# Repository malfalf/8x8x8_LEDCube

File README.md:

# 8x8x8_LEDCube
PCB con componentes necesarios para controlar un cubo de 8x8x8 LEDs RGB

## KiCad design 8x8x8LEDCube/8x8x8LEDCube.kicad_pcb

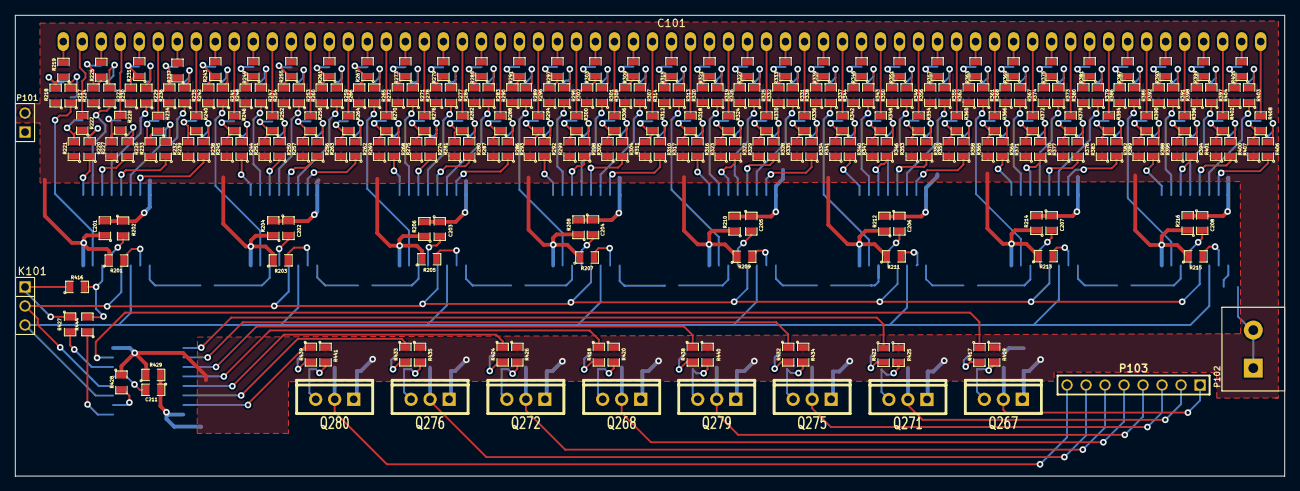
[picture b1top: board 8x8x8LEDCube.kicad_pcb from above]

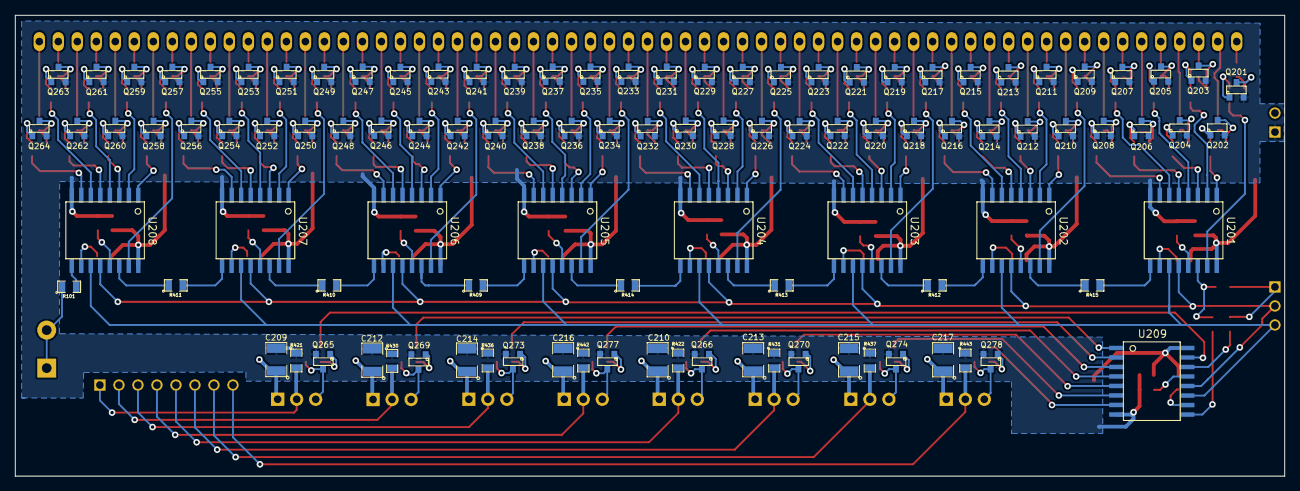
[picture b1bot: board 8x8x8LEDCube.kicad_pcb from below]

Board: 2 copper layers, 169.6 x 61.6 mm, 356 parts (105 on the bottom side), 330 nets.

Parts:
C101: CONNECTOR_1X64; 1x64_Connector_Receptade_2.54mm
C201, C202, C203, C204, C205, C206, C207, C208, C211: 0.1u; SM0805_NoVal
C209, C210, C212, C213, C214, C215, C216, C217: 47U; SM1210
K101: CONN_3; PIN_ARRAY_3X1
P101: CONN_2; PIN_ARRAY_2X1
P102: CONN_2; Terminal_Block_200mil_5mm
P103: CONN_8; PIN_ARRAY_8x1
Q201, Q202, Q203, Q204, Q205, Q206, Q207, Q208, Q209, Q210, Q211, Q212, Q213, Q214, Q215, Q216, Q217, Q218, Q219, Q220, Q221, Q222, Q223, Q224, Q225, Q226, Q227, Q228, Q229, Q230, Q231, Q232, Q233, Q234, Q235, Q236, Q237, Q238, Q239, Q240, Q241, Q242, Q243, Q244, Q245, Q246, Q247, Q248, Q249, Q250, Q251, Q252, Q253, Q254, Q255, Q256, Q257, Q258, Q259, Q260, Q261, Q262, Q263, Q264, Q265, Q266, Q269, Q270, Q273, Q274, Q277, Q278: NPN; SOT23_NPN_MMBT3904
Q267, Q268, Q271, Q272, Q275, Q276, Q279, Q280: IRF9540N; TO220_IRF9540N
R101, R201, R202, R203, R204, R205, R206, R207, R208, R209, R210, R211, R212, R213, R214, R215, R216, R409, R410, R411, R412, R413, R414, R415, R416, R427, R428, R429, R444: 0; SM0805_NoVal
R217, R218, R220, R221, R223, R224, R226, R227, R229, R230, R232, R233, R235, R236, R238, R239, R241, R242, R244, R245, R247, R248, R250, R251, R253, R254, R256, R257, R259, R260, R262, R263, R265, R266, R268, R269, R271, R272, R274, R275, R277, R278, R280, R281, R283, R284, R286, R287, R289, R290, R292, R293, R295, R296, R298, R299, R301, R302, R304, R305, R307, R308, R310, R311, R313, R314, R316, R317, R319, R320, R322, R323, R325, R326, R328, R329, R331, R332, R334, R335, R337, R338, R340, R341, R343, R344, R346, R347, R349, R350, R352, R353, R355, R356, R358, R359, R361, R362, R364, R365, R367, R368, R370, R371, R373, R374, R376, R377, R379, R380, R382, R383, R385, R386, R388, R389, R391, R392, R394, R395, R397, R398, R400, R401, R403, R404, R406, R407, R417, R418, R419, R420, R423, R424, R425, R426, R432, R433, R434, R435, R438, R439, R440, R441: 1K; SM0805_NoVal
R219, R222, R225, R228, R231, R234, R237, R240, R243, R246, R249, R252, R255, R258, R261, R264, R267, R270, R273, R276, R279, R282, R285, R288, R291, R294, R297, R300, R303, R306, R309, R312, R315, R318, R321, R324, R327, R330, R333, R336, R339, R342, R345, R348, R351, R354, R357, R360, R363, R366, R369, R372, R375, R378, R381, R384, R387, R390, R393, R396, R399, R402, R405, R408, R421, R422, R430, R431, R436, R437, R442, R443: 100; SM0805_NoVal
U201, U202, U203, U204, U205, U206, U207, U208, U209: SN74HC595DWR; SOIC16_SN74HC595DWR

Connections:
/AnodeControl/AnodeP1: P103.1, Q267.D, R421.2
/AnodeControl/AnodeP2: P103.2, Q271.D, R430.2
/AnodeControl/AnodeP3: P103.3, Q275.D, R436.2
/AnodeControl/AnodeP4: P103.4, Q279.D, R442.2
/AnodeControl/AnodeP5: P103.5, Q268.D, R422.2
/AnodeControl/AnodeP6: P103.6, Q272.D, R431.2
/AnodeControl/AnodeP7: P103.7, Q276.D, R437.2
/AnodeControl/AnodeP8: P103.8, Q280.D, R443.2
/ColorControl/C1Red: C101.1, R219.2
/ColorControl/C2Red: C101.2, R222.2
/ColorControl/C3Red: C101.3, R225.2
/ColorControl/C4Red: C101.4, R228.2
/ColorControl/C5Red: C101.5, R231.2
/ColorControl/C6Red: C101.6, R234.2
/ColorControl/C7Red: C101.7, R237.2
/ColorControl/C8Red: C101.8, R240.2
/ColorControl/C9Red: C101.9, R243.2
/ColorControl/C10Red: C101.10, R246.2
/ColorControl/C11Red: C101.11, R249.2
/ColorControl/C12Red: C101.12, R252.2
/ColorControl/C13Red: C101.13, R255.2
/ColorControl/C14Red: C101.14, R258.2
/ColorControl/C15Red: C101.15, R261.2
/ColorControl/C16Red: C101.16, R264.2
/ColorControl/C17Red: C101.17, R267.2
/ColorControl/C18Red: C101.18, R270.2
/ColorControl/C19Red: C101.19, R273.2
/ColorControl/C20Red: C101.20, R276.2
/ColorControl/C21Red: C101.21, R279.2
/ColorControl/C22Red: C101.22, R282.2
/ColorControl/C23Red: C101.23, R285.2
/ColorControl/C24Red: C101.24, R288.2
/ColorControl/C25Red: C101.25, R291.2
/ColorControl/C26Red: C101.26, R294.2
/ColorControl/C27Red: C101.27, R297.2
/ColorControl/C28Red: C101.28, R300.2
/ColorControl/C29Red: C101.29, R303.2
/ColorControl/C30Red: C101.30, R306.2
/ColorControl/C31Red: C101.31, R309.2
/ColorControl/C32Red: C101.32, R312.2
/ColorControl/C33Red: C101.33, R315.2
/ColorControl/C34Red: C101.34, R318.2
/ColorControl/C35Red: C101.35, R321.2
/ColorControl/C36Red: C101.36, R324.2
/ColorControl/C37Red: C101.37, R327.2
/ColorControl/C38Red: C101.38, R330.2
/ColorControl/C39Red: C101.39, R333.2
/ColorControl/C40Red: C101.40, R336.2
/ColorControl/C41Red: C101.41, R339.2
/ColorControl/C42Red: C101.42, R342.2
/ColorControl/C43Red: C101.43, R345.2
/ColorControl/C44Red: C101.44, R348.2
/ColorControl/C45Red: C101.45, R351.2
/ColorControl/C46Red: C101.46, R354.2
/ColorControl/C47Red: C101.47, R357.2
/ColorControl/C48Red: C101.48, R360.2
/ColorControl/C49Red: C101.49, R363.2
/ColorControl/C50Red: C101.50, R366.2
/ColorControl/C51Red: C101.51, R369.2
/ColorControl/C52Red: C101.52, R372.2
/ColorControl/C53Red: C101.53, R375.2
/ColorControl/C54Red: C101.54, R378.2
/ColorControl/C55Red: C101.55, R381.2
/ColorControl/C56Red: C101.56, R384.2
/ColorControl/C57Red: C101.57, R387.2
/ColorControl/C58Red: C101.58, R390.2
/ColorControl/C59Red: C101.59, R393.2
/ColorControl/C60Red: C101.60, R396.2
/ColorControl/C61Red: C101.61, R399.2
/ColorControl/C62Red: C101.62, R402.2
/ColorControl/C63Red: C101.63, R405.2
/ColorControl/C64Red: C101.64, R408.2
/ColorControl/NextColor: R101.2, U208.9
AnodePlane1: R417.1, U209.15
AnodePlane2: R423.1, U209.1
AnodePlane3: R432.1, U209.2
AnodePlane4: R438.1, U209.3
AnodePlane5: R418.1, U209.4
AnodePlane6: R424.1, U209.5
AnodePlane7: R433.1, U209.6
AnodePlane8: R439.1, U209.7
DATA_IN: K101.1, R416.1, R427.1
FIRST_COLOR: R444.1, U209.9
GND: C201.2, C202.2, C203.2, C204.2, C205.2, C206.2, C207.2, C208.2, C209.2, C210.2, C211.2, C212.2, C213.2, C214.2, C215.2, C216.2, C217.2, P101.1, Q201.1, Q202.1, Q203.1, Q204.1, Q205.1, Q206.1, Q207.1, Q208.1, Q209.1, Q210.1, Q211.1, Q212.1, Q213.1, Q214.1, Q215.1, Q216.1, Q217.1, Q218.1, Q219.1, Q220.1, Q221.1, Q222.1, Q223.1, Q224.1, Q225.1, Q226.1, Q227.1, Q228.1, Q229.1, Q230.1, Q231.1, Q232.1, Q233.1, Q234.1, Q235.1, Q236.1, Q237.1, Q238.1, Q239.1, Q240.1, Q241.1, Q242.1, Q243.1, Q244.1, Q245.1, Q246.1, Q247.1, Q248.1, Q249.1, Q250.1, Q251.1, Q252.1, Q253.1, Q254.1, Q255.1, Q256.1, Q257.1, Q258.1, Q259.1, Q260.1, Q261.1, Q262.1, Q263.1, Q264.1, Q265.1, Q266.1, Q269.1, Q270.1, Q273.1, Q274.1, Q277.1, Q278.1, R202.1, R204.1, R206.1, R208.1, R210.1, R212.1, R214.1, R216.1, R421.1, R422.1, R429.1, R430.1, R431.1, R436.1, R437.1, R442.1, R443.1, U201.8, U202.8, U203.8, U204.8, U205.8, U206.8, U207.8, U208.8, U209.8
LATCH: K101.2, U201.12, U202.12, U203.12, U204.12, U205.12, U206.12, U207.12, U208.12, U209.12
unnamed: P102.1, P102.2, R101.1
unnamed: Q237.3, R326.2, R327.1
unnamed: Q237.2, R325.2
unnamed: Q238.2, R328.2
unnamed: Q235.2, R319.2
unnamed: Q235.3, R320.2, R321.1
unnamed: Q236.3, R323.2, R324.1
unnamed: Q236.2, R322.2
unnamed: Q233.3, R314.2, R315.1
unnamed: Q233.2, R313.2
unnamed: Q234.2, R316.2
unnamed: Q234.3, R317.2, R318.1
unnamed: Q239.2, R331.2
unnamed: Q240.3, R335.2, R336.1
unnamed: Q240.2, R334.2
unnamed: Q230.3, R305.2, R306.1
unnamed: Q238.3, R329.2, R330.1
unnamed: Q241.3, R338.2, R339.1
unnamed: Q244.3, R347.2, R348.1
unnamed: Q244.2, R346.2
unnamed: Q245.3, R350.2, R351.1
unnamed: Q241.2, R337.2
unnamed: Q242.3, R341.2, R342.1
unnamed: Q242.2, R340.2
unnamed: Q243.2, R343.2
unnamed: Q243.3, R344.2, R345.1
unnamed: Q239.3, R332.2, R333.1
unnamed: Q255.2, R379.2
unnamed: Q224.3, R287.2, R288.1
unnamed: Q224.2, R286.2
unnamed: Q222.3, R281.2, R282.1
unnamed: Q222.2, R280.2
unnamed: Q217.2, R265.2
unnamed: Q223.3, R284.2, R285.1
unnamed: Q223.2, R283.2
unnamed: Q221.2, R277.2
unnamed: Q221.3, R278.2, R279.1
unnamed: Q220.3, R275.2, R276.1
unnamed: Q217.3, R266.2, R267.1
unnamed: Q218.2, R268.2
unnamed: Q218.3, R269.2, R270.1
unnamed: Q219.2, R271.2
unnamed: Q219.3, R272.2, R273.1
unnamed: Q220.2, R274.2
unnamed: Q228.2, R298.2
unnamed: Q226.3, R293.2, R294.1
unnamed: Q227.2, R295.2
unnamed: Q227.3, R296.2, R297.1
unnamed: Q226.2, R292.2
unnamed: Q228.3, R299.2, R300.1
unnamed: Q229.2, R301.2
unnamed: Q229.3, R302.2, R303.1
unnamed: Q232.2, R310.2
unnamed: Q225.2, R289.2
unnamed: Q225.3, R290.2, R291.1
unnamed: Q230.2, R304.2
unnamed: Q231.2, R307.2
unnamed: Q231.3, R308.2, R309.1
unnamed: Q232.3, R311.2, R312.1
unnamed: Q261.3, R398.2, R399.1
unnamed: Q261.2, R397.2
unnamed: Q262.3, R401.2, R402.1
unnamed: Q262.2, R400.2
unnamed: Q258.2, R388.2
unnamed: Q259.2, R391.2
unnamed: Q259.3, R392.2, R393.1
unnamed: Q260.2, R394.2
unnamed: Q260.3, R395.2, R396.1
unnamed: Q257.2, R385.2
unnamed: Q257.3, R386.2, R387.1
unnamed: Q258.3, R389.2, R390.1
unnamed: Q263.3, R404.2, R405.1
unnamed: Q263.2, R403.2
unnamed: Q264.3, R407.2, R408.1
unnamed: Q264.2, R406.2
unnamed: Q254.3, R377.2, R378.1
unnamed: R413.2, U203.9
unnamed: R414.2, U204.9
unnamed: R409.2, U205.9
unnamed: R410.2, U206.9
unnamed: R411.2, U207.9
unnamed: R416.2, R444.2, U201.14
unnamed: R415.2, U201.9
unnamed: Q248.2, R358.2
unnamed: Q248.3, R359.2, R360.1
unnamed: Q245.2, R349.2
unnamed: Q246.2, R352.2
unnamed: Q246.3, R353.2, R354.1
unnamed: Q247.2, R355.2
unnamed: Q247.3, R356.2, R357.1
unnamed: Q251.3, R368.2, R369.1
unnamed: Q250.2, R364.2
unnamed: Q250.3, R365.2, R366.1
unnamed: Q251.2, R367.2
unnamed: Q249.3, R362.2, R363.1
unnamed: Q252.2, R370.2
unnamed: Q252.3, R371.2, R372.1
unnamed: Q253.2, R373.2
unnamed: Q256.3, R383.2, R384.1
unnamed: Q256.2, R382.2
unnamed: Q253.3, R374.2, R375.1
unnamed: Q249.2, R361.2
unnamed: Q254.2, R376.2
unnamed: Q255.3, R380.2, R381.1
unnamed: Q206.2, R232.2
unnamed: Q205.3, R230.2, R231.1
unnamed: Q205.2, R229.2
unnamed: Q204.3, R227.2, R228.1
unnamed: Q204.2, R226.2
unnamed: Q203.3, R224.2, R225.1
unnamed: Q203.2, R223.2
unnamed: Q202.3, R221.2, R222.1
unnamed: Q202.2, R220.2
unnamed: Q201.3, R218.2, R219.1
unnamed: Q208.3, R239.2, R240.1
unnamed: Q208.2, R238.2
unnamed: Q207.3, R236.2, R237.1
unnamed: Q207.2, R235.2
unnamed: R415.1, U202.14
unnamed: R412.2, U202.9
unnamed: Q201.2, R217.2
unnamed: R411.1, U208.14
unnamed: R410.1, U207.14
unnamed: R409.1, U206.14
unnamed: R414.1, U205.14
unnamed: R413.1, U204.14
unnamed: R412.1, U203.14
unnamed: R202.2, U201.13
unnamed: R201.2, U201.10
unnamed: Q206.3, R233.2, R234.1
unnamed: R204.2, U202.13
unnamed: R207.2, U204.10
unnamed: R206.2, U203.13
unnamed: R210.2, U205.13
unnamed: R209.2, U205.10
unnamed: R208.2, U204.13
unnamed: R203.2, U202.10
unnamed: R213.2, U207.10
unnamed: R212.2, U206.13
unnamed: R216.2, U208.13
unnamed: R215.2, U208.10
unnamed: Q212.3, R251.2, R252.1
unnamed: Q212.2, R250.2
unnamed: Q211.3, R248.2, R249.1
unnamed: Q211.2, R247.2
unnamed: Q210.3, R245.2, R246.1
unnamed: Q210.2, R244.2
unnamed: Q209.3, R242.2, R243.1
unnamed: Q209.2, R241.2
unnamed: Q216.3, R263.2, R264.1
unnamed: Q216.2, R262.2
unnamed: Q215.3, R260.2, R261.1
unnamed: Q215.2, R259.2
unnamed: Q214.2, R256.2
unnamed: Q213.3, R254.2, R255.1
unnamed: Q213.2, R253.2
unnamed: Q214.3, R257.2, R258.1
unnamed: R211.2, U206.10
unnamed: R214.2, U207.13
unnamed: R205.2, U203.10
unnamed: Q269.2, R423.2
unnamed: Q269.3, Q271.G, R425.2
unnamed: Q273.2, R432.2
unnamed: Q273.3, Q275.G, R434.2
unnamed: R427.2, U209.14
unnamed: R429.2, U209.13
unnamed: R428.2, U209.10
unnamed: Q265.2, R417.2
unnamed: Q265.3, Q267.G, R419.2
unnamed: Q274.2, R433.2
unnamed: Q274.3, Q276.G, R435.2
unnamed: Q278.3, Q280.G, R441.2
unnamed: Q278.2, R439.2
unnamed: Q266.2, R418.2
unnamed: Q277.2, R438.2
unnamed: Q277.3, Q279.G, R440.2
unnamed: Q270.2, R424.2
unnamed: Q270.3, Q272.G, R426.2
unnamed: Q266.3, Q268.G, R420.2
RedC1: R217.1, U201.15
RedC2: R220.1, U201.1
RedC3: R223.1, U201.2
RedC4: R226.1, U201.3
RedC5: R229.1, U201.4
RedC6: R232.1, U201.5
RedC7: R235.1, U201.6
RedC8: R238.1, U201.7
RedC9: R241.1, U202.15
RedC10: R244.1, U202.1
RedC11: R247.1, U202.2
RedC12: R250.1, U202.3
RedC13: R253.1, U202.4
RedC14: R256.1, U202.5
RedC15: R259.1, U202.6
RedC16: R262.1, U202.7
RedC17: R265.1, U203.15
RedC18: R268.1, U203.1
RedC19: R271.1, U203.2
RedC20: R274.1, U203.3
RedC21: R277.1, U203.4
RedC22: R280.1, U203.5
RedC23: R283.1, U203.6
RedC24: R286.1, U203.7
RedC25: R289.1, U204.15
RedC26: R292.1, U204.1
RedC27: R295.1, U204.2
RedC28: R298.1, U204.3
RedC29: R301.1, U204.4
RedC30: R304.1, U204.5
RedC31: R307.1, U204.6
RedC32: R310.1, U204.7
RedC33: R313.1, U205.15
RedC34: R316.1, U205.1
RedC35: R319.1, U205.2
RedC36: R322.1, U205.3
RedC37: R325.1, U205.4
RedC38: R328.1, U205.5
RedC39: R331.1, U205.6
RedC40: R334.1, U205.7
RedC41: R337.1, U206.15
RedC42: R340.1, U206.1
RedC43: R343.1, U206.2
RedC44: R346.1, U206.3
RedC45: R349.1, U206.4
RedC46: R352.1, U206.5
RedC47: R355.1, U206.6
RedC48: R358.1, U206.7
RedC49: R361.1, U207.15
RedC50: R364.1, U207.1
RedC51: R367.1, U207.2
RedC52: R370.1, U207.3
RedC53: R373.1, U207.4
RedC54: R376.1, U207.5
RedC55: R379.1, U207.6
RedC56: R382.1, U207.7
RedC57: R385.1, U208.15
RedC58: R388.1, U208.1
RedC59: R391.1, U208.2
RedC60: R394.1, U208.3
RedC61: R397.1, U208.4
RedC62: R400.1, U208.5
RedC63: R403.1, U208.6
RedC64: R406.1, U208.7
SRCLK: K101.3, U201.11, U202.11, U203.11, U204.11, U205.11, U206.11, U207.11, U208.11, U209.11
VCC: C201.1, C202.1, C203.1, C204.1, C205.1, C206.1, C207.1, C208.1, C209.1, C210.1, C211.1, C212.1, C213.1, C214.1, C215.1, C216.1, C217.1, P101.2, Q267.S, Q268.S, Q271.S, Q272.S, Q275.S, Q276.S, Q279.S, Q280.S, R201.1, R203.1, R205.1, R207.1, R209.1, R211.1, R213.1, R215.1, R218.1, R221.1, R224.1, R227.1, R230.1, R233.1, R236.1, R239.1, R242.1, R245.1, R248.1, R251.1, R254.1, R257.1, R260.1, R263.1, R266.1, R269.1, R272.1, R275.1, R278.1, R281.1, R284.1, R287.1, R290.1, R293.1, R296.1, R299.1, R302.1, R305.1, R308.1, R311.1, R314.1, R317.1, R320.1, R323.1, R326.1, R329.1, R332.1, R335.1, R338.1, R341.1, R344.1, R347.1, R350.1, R353.1, R356.1, R359.1, R362.1, R365.1, R368.1, R371.1, R374.1, R377.1, R380.1, R383.1, R386.1, R389.1, R392.1, R395.1, R398.1, R401.1, R404.1, R407.1, R419.1, R420.1, R425.1, R426.1, R428.1, R434.1, R435.1, R440.1, R441.1, U201.16, U202.16, U203.16, U204.16, U205.16, U206.16, U207.16, U208.16, U209.16

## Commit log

2015-12-11 Empezando el esquemático, añadido el footprint del shift register y haciendo pruebas de pcb
2016-01-24 Final version of the PCB
